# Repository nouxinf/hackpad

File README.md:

# hackpad

This is my submission for the hackpad mission! This is my first time using KiCad and Autodesk Fusion so I'm not very experienced. Decided to make this because I wanted to make some automation easier, as it binds the keys to F13-19, which are unused usually.

It also includes a bongo cat animation, that activates when you press any key on the macropad. Code is from github over [here](https://github.com/qmk/qmk_firmware/pull/19334/changes).

## Specifications

- Xiao RP2040
- 7 keys
- 0.91' OLED Display

## Bill of Materials

| **Name**                          | **Quantity** |
| --------------------------------- | ------------ |
| Seeed XIAO RP2040 microcontroller | 1            |
| MX-style mechanical switches      | 7            |
| 0.91" 128x32 OLED Display         | 1            |
| Blank DSA keycaps                 | 7            |
| M3x16mm Screws                    | 4            |
| M3x5x4mm heatset inserts          | 4            |
| PCB                               | 1            |
| Case                              | 1            |

Also available in `bom.csv`

## Images

_The case assembled (top part made transparent for visibility, not in actual model)_

_Schematic of the PCB_

_PCB design_

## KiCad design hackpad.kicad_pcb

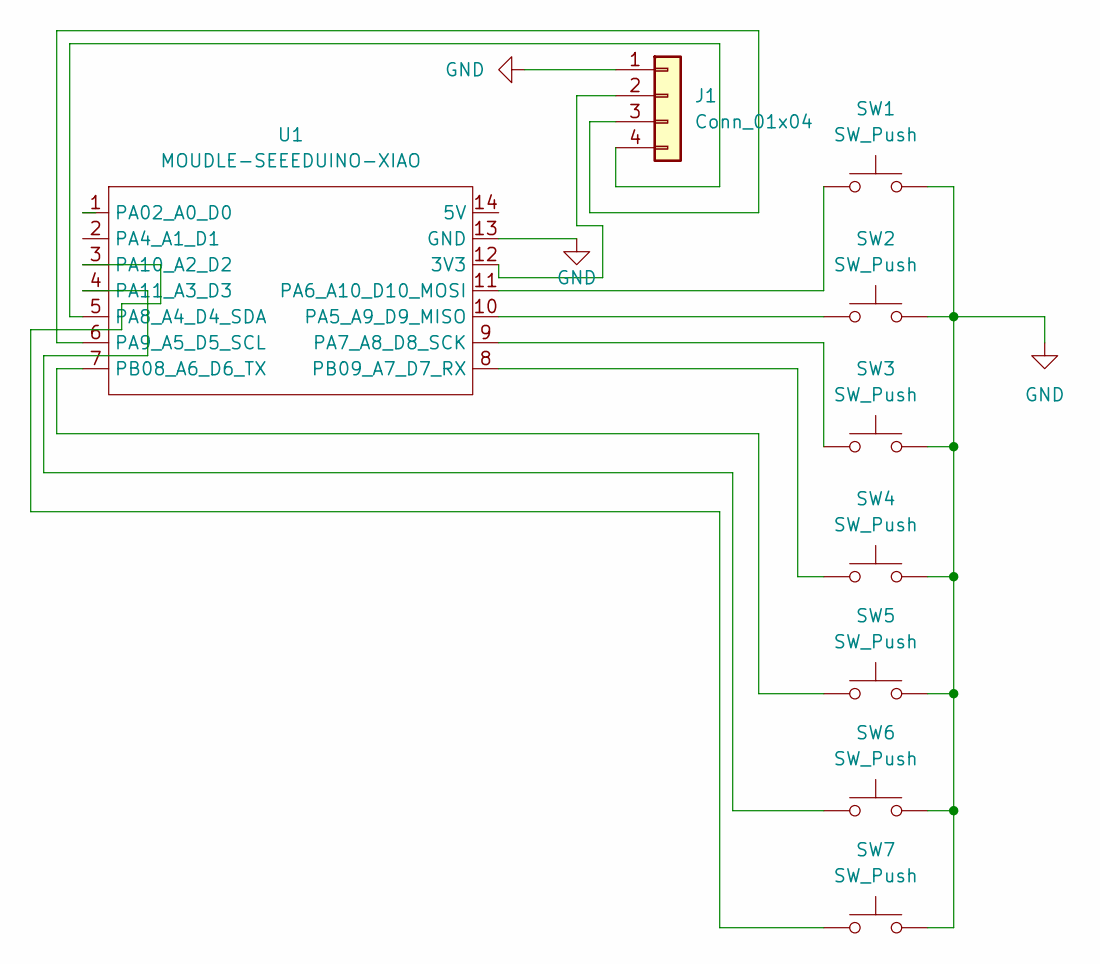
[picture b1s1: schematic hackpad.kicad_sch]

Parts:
J1: Conn_01x04; ER_OLEDM0.91_1x-I2C
SW1, SW2, SW3, SW4, SW5, SW6, SW7: SW_Push; SW_Cherry_MX_1.00u_PCB
U1: MOUDLE-SEEEDUINO-XIAO; XIAO-Generic-Hybrid-14P-2.54-21X17.8MM

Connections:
GND: J1.1 (GND), SW1.2, SW2.2, SW3.2, SW4.2, SW5.2, SW6.2, SW7.2, U1.13 (GND)
unnamed: J1.2, U1.12 (3V3)
unnamed: J1.3, U1.6 (PA9_A5_D5_SCL)
unnamed: J1.4, U1.5 (PA8_A4_D4_SDA)
unnamed: SW2.1, U1.10 (PA5_A9_D9_MISO)
unnamed: SW1.1, U1.11 (PA6_A10_D10_MOSI)
unnamed: SW3.1, U1.9 (PA7_A8_D8_SCK)
unnamed: SW7.1, U1.3 (PA10_A2_D2)
unnamed: SW6.1, U1.4 (PA11_A3_D3)
unnamed: SW5.1, U1.7 (PB08_A6_D6_TX)
unnamed: SW4.1, U1.8 (PB09_A7_D7_RX)

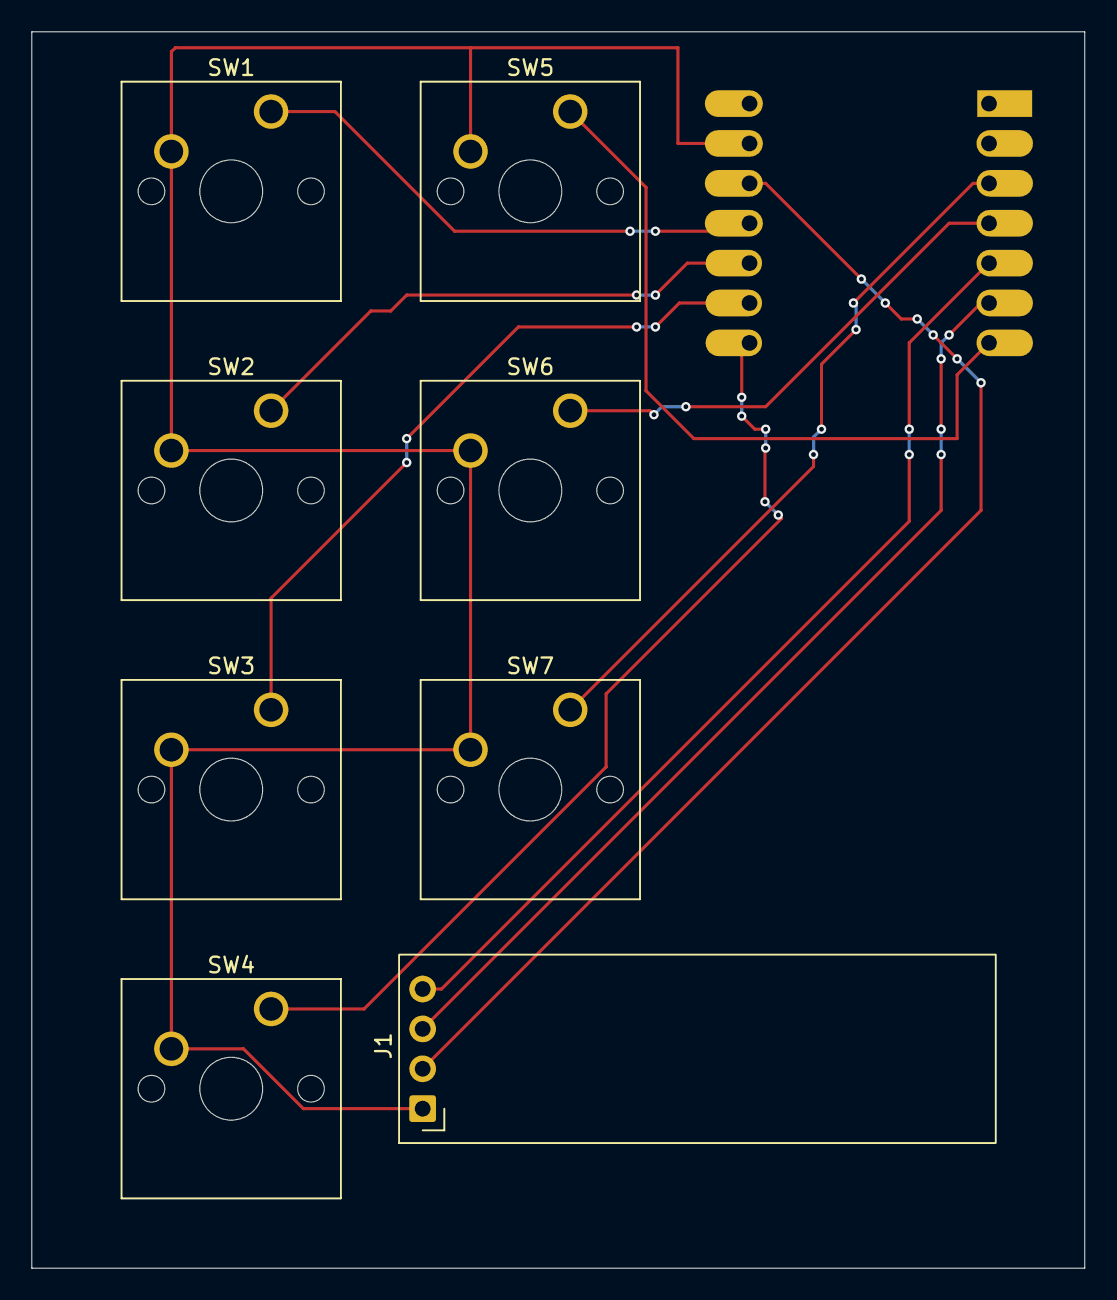
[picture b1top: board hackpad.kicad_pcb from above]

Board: 2 copper layers, 67.1 x 78.7 mm, 9 parts (1 on the bottom side), 11 nets.

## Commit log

2026-06-09 add project files
2026-06-11 update pcb, add case files
2026-06-12 reorganise files, firmware
2026-06-12 cleanup files
2026-06-12 update gerbers
2026-06-12 readme
2026-06-12 credits for bongo cat
2026-06-12 describe f key feature
